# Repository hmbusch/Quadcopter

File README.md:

Quadcopter
==========

A quadcopter of my own design

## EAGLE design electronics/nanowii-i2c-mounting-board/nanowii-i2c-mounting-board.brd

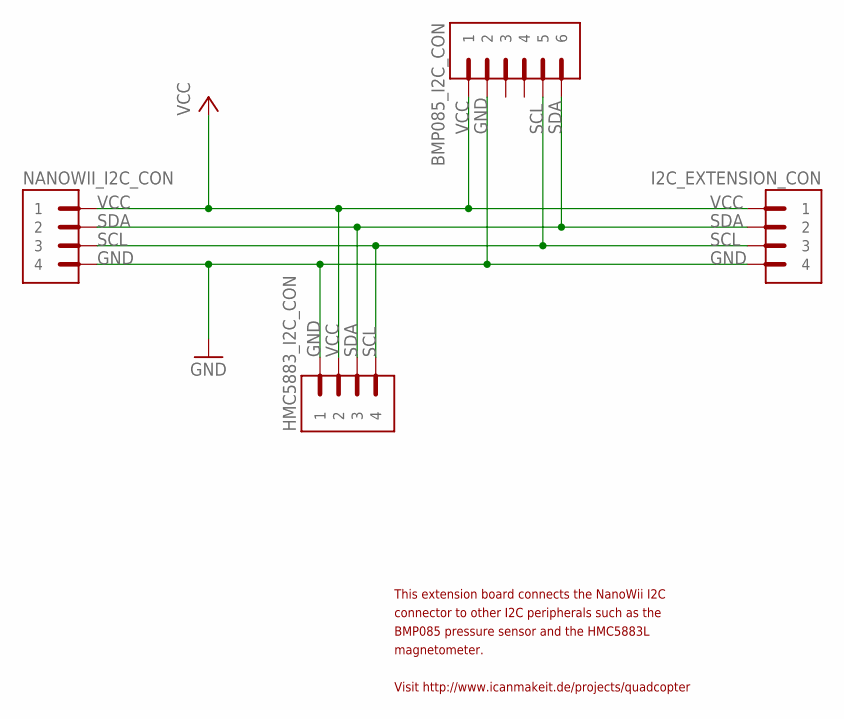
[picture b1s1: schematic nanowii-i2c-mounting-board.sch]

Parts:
BMP085_I2C_CON: PIN_HEADER_6-WIDE; BREAKAWAY_STRAIGHT_6_WIDE
HMC5883_I2C_CON: PIN_HEADER_4-WIDE; BREAKAWAY_STRAIGHT_4_WIDE
I2C_EXTENSION_CON: PIN_HEADER_4-WIDE; BREAKAWAY_STRAIGHT_4_WIDE
NANOWII_I2C_CON: PIN_HEADER_4-WIDE; BREAKAWAY_STRAIGHT_4_WIDE

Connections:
GND: BMP085_I2C_CON.2, HMC5883_I2C_CON.1, I2C_EXTENSION_CON.4, NANOWII_I2C_CON.4
SCL: BMP085_I2C_CON.5, HMC5883_I2C_CON.4, I2C_EXTENSION_CON.3, NANOWII_I2C_CON.3
SDA: BMP085_I2C_CON.6, HMC5883_I2C_CON.3, I2C_EXTENSION_CON.2, NANOWII_I2C_CON.2
VCC: BMP085_I2C_CON.1, HMC5883_I2C_CON.2, I2C_EXTENSION_CON.1, NANOWII_I2C_CON.1

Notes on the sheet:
This extension board connects the NanoWii I2C
connector to other I2C peripherals such as the
BMP085 pressure sensor and the HMC5883L
magnetometer.
Visit http://www.icanmakeit.de/projects/quadcopter

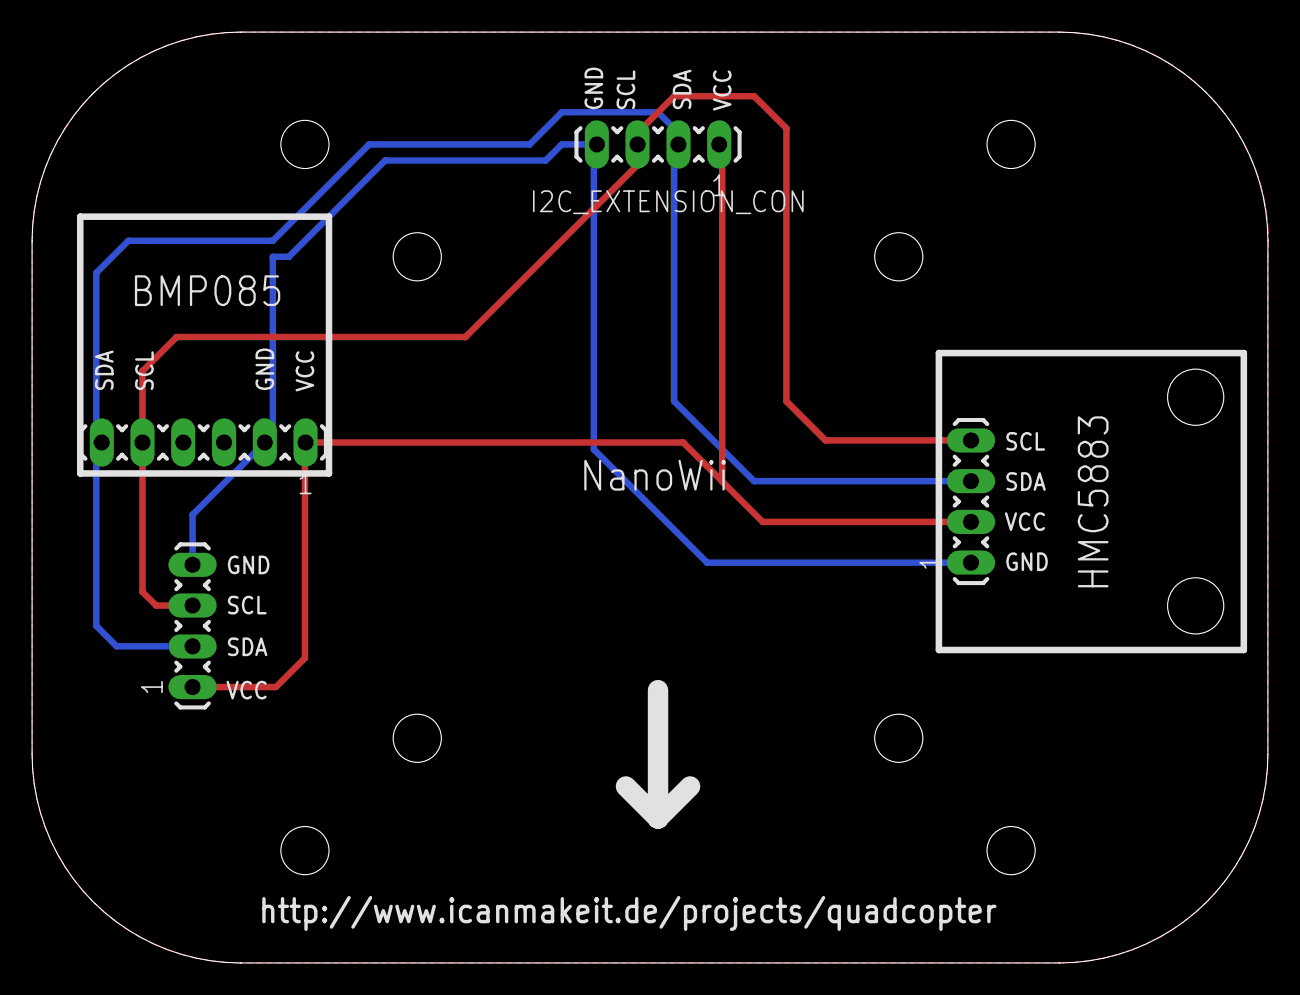
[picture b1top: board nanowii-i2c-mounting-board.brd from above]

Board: 2 copper layers, 77.0 x 58.0 mm, 4 parts (0 on the bottom side), 4 nets.

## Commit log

2012-06-23 Created a nearly accurate drawing of the mounting plate of a Turnigy Park300 1080kv brushless motor.
2012-06-23 Edited the metadata of the file
2012-06-25 Designed a boom mount for the arms
    Created a boom mounting plate using the previously designed motor
    mounting plate and two tube clamps for 16mm tubes. The design is not
    (yet?) a valid 2D model for laser cutting, only for printing.
2012-06-27 Created the center plates
    Created a top and bottom center plate. Each copter arm will be held by 3
    tube clamps, two on the bottom plate, another on the top plate. In
    future versions, mounting holes for the controller board will be added
    as well as slots for attaching the battery with velcro tape and the ESCs
    with cable binders.
2012-06-28 Modified the document metadata
2012-06-28 Created a new version of the center plate
    This version was designed from scratch making extensive use of
    construction help. No guessing and estimating was used during the creation
    process, everything relies on symmetry.
2012-06-28 Created new top & bottom plates using the template
    The newly created template was used to create a new set of center plates.
    For now, only the drill holes for mounting the boom clamps were created,
    assuming 14.2x23mm clamps for 16mm tubes. The drill holes are 4.1mm in
    diameter and suitable for M4 bolts.
    Further holes to mount the PCB and slots to attach the battery and the ESC
    are supposed to follow.
2012-06-29 Converted all drawings to AutoCAD R14 format
    The files were originally created using a demo version of TurboCAD 2D/3D
    Deluxe 19, which turned out to be too expensive to buy so I acquired a
    copy of TurboCAD 2D 16 at a much cheaper price. But Version 16 can't open
    version 19s files and version 19 can only export down to version 17 (which
    in turn again can't be opened by version 16), so I chose to export all
    files to an older AutoCAD format that can be read by version 16 so I would
2012-06-30 Converted from v19 files to v16 ones using the DWG files
2012-06-30 Reorganised the files
2012-06-30 Created a new center plate template for the diy model from scratch
2012-06-30 Deleted the DWG files as they will be out of date soon
2012-06-30 Created a new version of the bottom center plate using the new template
2012-07-15 Added drill holes for the cable binders holding the ESCs
2012-07-15 Created a new version of the top center plate
    This version was created using the newly created template. Bottom and top
    plate are now precisely chamfered at the edges.
2012-07-18 Fixed a misplaced hole
    One of the hole used to attach the ESC to the plate was misplaced by a few
    millimeters. This has been fixed.
2012-07-19 Added holes for the battery mount
    The battery will be mounted on a separate plate that will be attached to
    the bottom plate via M3 screws with a spacing between the screws large
    enough to accommodate batteries with a width up to 65mm.
    Also added a lot of measurement labels on a separate layer for information
    purposes.
2012-07-21 Created a battery mounting plate
    THe plate measures 9x9cm and is supposed to be attached to the bottom face
    side of the bottom center plate, using some spacers to provide room for
    sliding a piece of velcro tape through it. The plate is deisgned as a
    frame in order so save weight.
2012-07-21 Moved the holes for the battery mount
    In order for the holes on the battery mount to be centered, the holes in
    the bottom plate needed to be moved slightly.
2012-07-21 Enlarged the holes for the battery mount
    The battery mount will now be attached to the bottom center plate using M6
    plastic screws with 50mm length that will also double as a landing support
    for the center part of the copter. Thus the mounting holes on both plated
    were enlarged to 6mm.
2012-07-21 Added a new measurement
2012-07-21 Added mounting holes for the electronics
    Added 3mm mounting holes to hold the power distribution board and the
    flight control module. Also added a meaurements layer.
2012-07-21 Readjusted mounting holes
    The first chosen measure for the electronic mounting holes was a little
    off. This has been corrected.
2012-07-21 Added mounting holes for the X configuration
    With this additional set of holes, the plate can now be used to mount the
    flight control and the receiver in either + or X configuration. The reason
    why the receiver mounting holes differ is that the flight control leaves
    less space on the side between the booms for the receiver.
2012-08-10 Removed receiver mounting holes, added cutting aids
    The receiver is now mounted in a food storage container mounted on top of
    the quadcopter. The mounting holes have therefor been removed.
    Some additional lines to help cutting the plate were added.
2012-08-10 Added some cutting aids
2012-08-12 Added experimental boom drawing
    I've added the booms to the drawing for better understanding. They are
    located on another layer and can easily be hidden. The booms use an
    experimental layout with one long and two short ones instead of 4 short
    ones.
2012-08-12 Recreated the motor mounting plate from scratch
    The previous version was not exact enough as it was not designed using
    exact measures and construction lines. This new mounting plate now only
    features the drilling holes and no component outlines.
2012-08-12 Modified file description
2012-08-12 Created template for the holes on a boom
2012-08-12 Derived a SVG file from the boom template for printing all 4 booms at once
2012-08-12 Inserted 3 additional copies of the mounting plate for more efficient printing
2012-08-18 Quadrupled the boom drawing for better printing
2012-09-20 Created a PCB to mount the NanoWii and sensors.
    This PCB features the mounting holes required to attach it to the center
    plate and additional ones to hold the NanoWii flight controller and the
    Sparkfun 9DOF stick.
    The PCB provides an I2C bus connection for the NanoWii, the BMP085
    pressure sensor (Sparkfun breakout version) and the 9DOF stick (also
    Sparkfun breakout version). From the 9DOF stick, only the compass will be
2013-03-09 Added etch mask image for the i2c board
    This is intended for single side home etching.
2013-03-09 Replaced the 9DOF stick with single HMC5883 breakout
    Unfortunately, the 9DOF stick interfered with the NanoWii's own sensors on
    the I2C bus. As the HMC5883 magnometer was the only sensor really needed
    from the stick, the design was changed to accomodate a single 5883
    breakout (from Sparkfun) instead of the 9DOF stick.
    The PCB was also changed to double sided and is now intended for
    professional manufacturing.
2013-03-09 Applied DRU for elecfreaks.com manufacturing and created gerber files
2013-06-17 Started working on a simple 35cm frame
    This frame is intended for my medium sized quadcopter. It is a simple design with an upper and a lower base plate and four rectangular boom. This is my "all-in-one" drawing and it currently only mode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
2013-07-03 Created seperate file for the lower base plate
2013-07-05 Added drilling template for the booms
    Also renamed the lower base plate file.
2013-07-14 Added the upper base plate
2013-07-14 Added drill holes for battery mounting plate
2013-07-14 Created a simple plate for mounting the battery.
    With the screws and the landing gear on the bottom side, I needed an even
    surface to attach the battery to. In case of a crash, screws, nuts, etc.
    now won't directly punch into the battery.
2013-07-14 A plate that goes on top of the electronics tower
2014-04-13 Layout for a 40cm wooden H-Quad added
    See http://www.icanmakeit.de/tag/h-quad/ for more details.
2014-04-13 Designed a mounting bracket for the F550
    I purchased a landing gear that could only be fitted to the
    F550 using a custom made mounting bracket out of aluminum.

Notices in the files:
parts and their libraries:
icmi-connectors: ICMI Custom Parts for EAGLE by Hendrik Busch is licensed under a Creative Commons Attribution-NonCommercial-ShareAlike 3.0 Germany License.
